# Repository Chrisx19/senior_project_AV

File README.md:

# CPP Senior Project

## December 2022 - May 2023
ROS Noetic control GPS autonomous vehicle using ATMega2560 and Jetson Nano. 

## Video Demo
**Autonomous Mode:**        https://youtu.be/Os8QsEWLSAU

**Controller Mode:**        https://youtu.be/IqCc2zWrYO0

**Test Controller Mode:**   https://youtu.be/60IaMCZQ1AA

### Mechanical 

### Electrical

**PCB Design**
  Reason initial design is included because of the mistakes my team learned while testing. Due to small traces with about 3 Amps going inside of our traces, it blew up and it came out of the PCB. Therefore, we learned from mistakes and calculated how much mil we need for our traces that can withstand about 4 Amps.
  
* **Initial Design: 30 mil traces**

* **Final Design: 150 mil traces**

### Software 
* **Communication:** 
  In order to have Jetson Nano and ATMega2560 talk to each other bi directionally, we used a customed UART protocol from ROS package called 'Rosserial.' Rosserial protocol was able to give us the ncecesity we need to transfer data from each other while autonomy. With rosserial, ATMega2560 became its own node and Jetson Nano has its main node and sub node. Nodes are basically scripts, which transfer myriad of data types from node to node.

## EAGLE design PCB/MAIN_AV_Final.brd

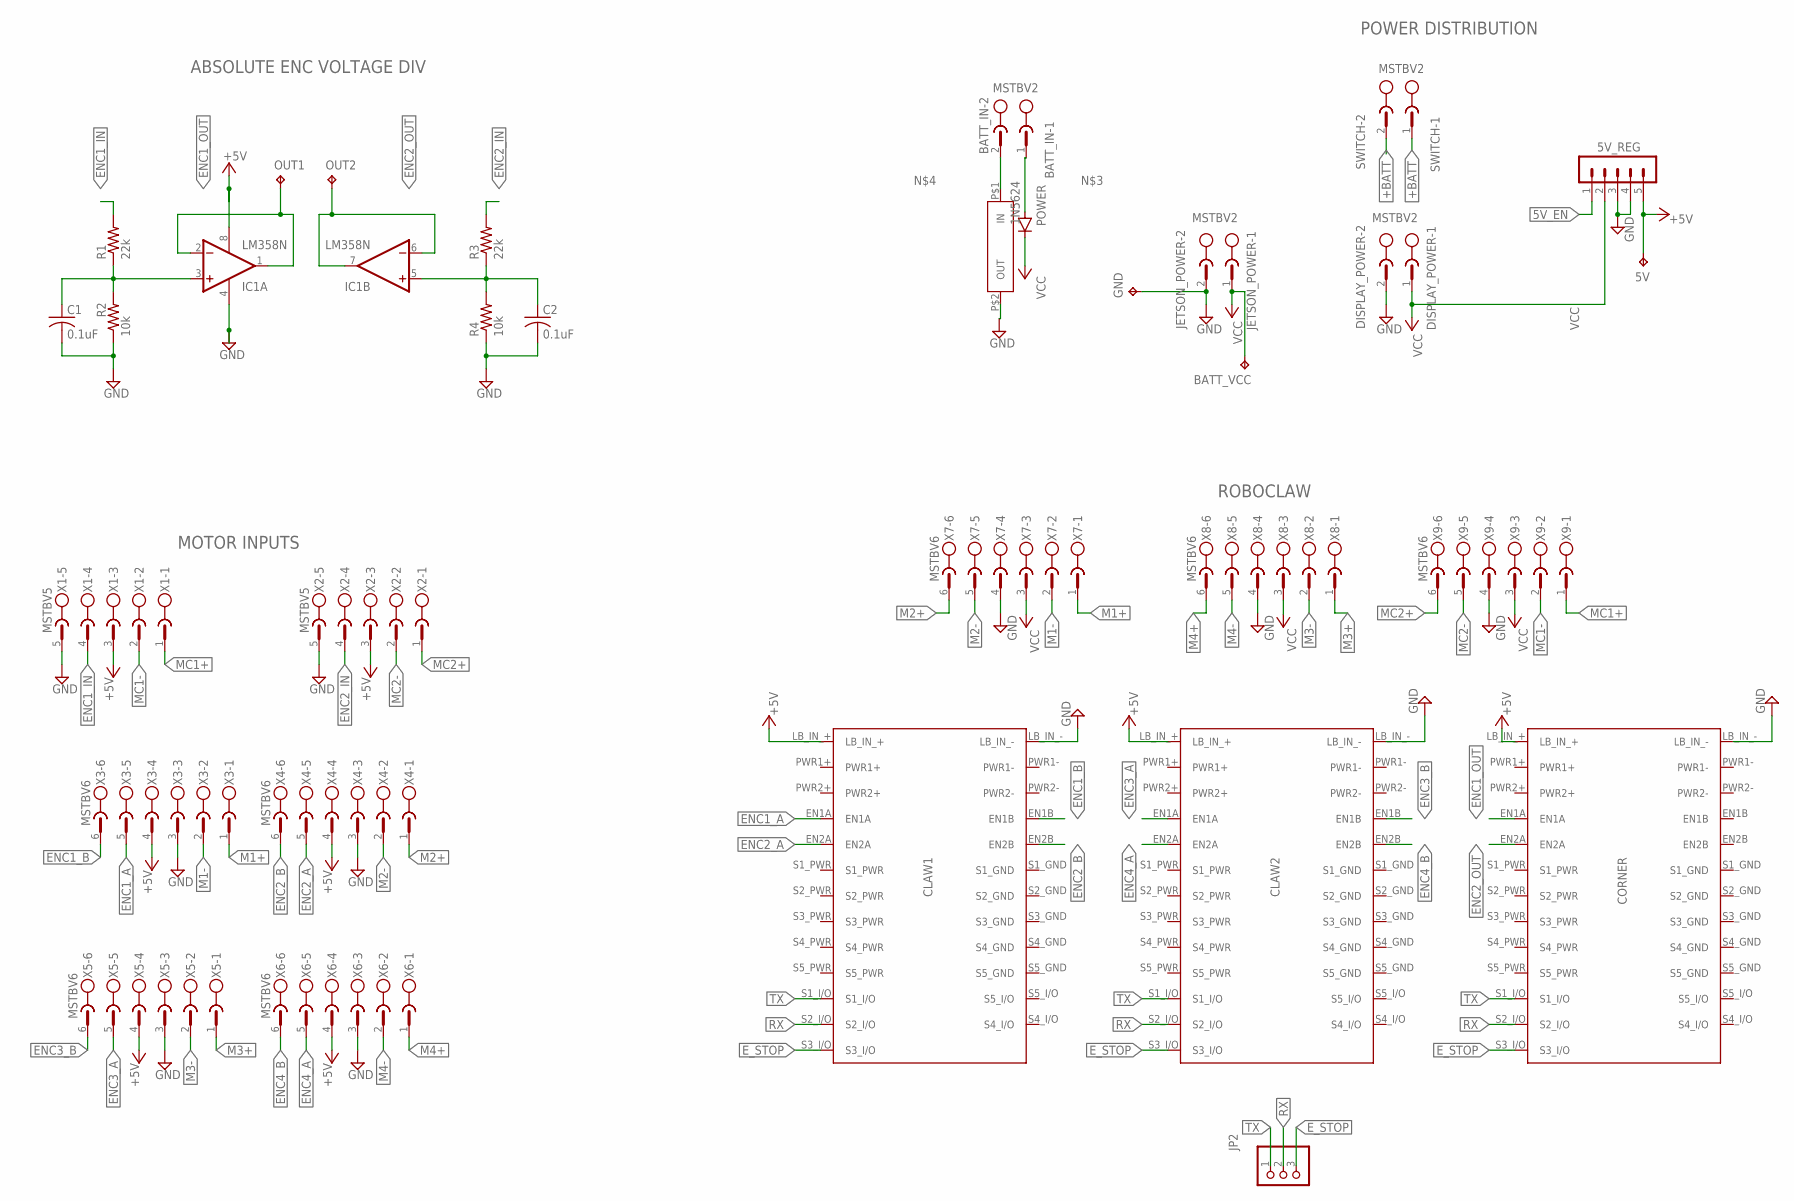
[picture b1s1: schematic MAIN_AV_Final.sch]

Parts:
5V: TPTP10SQ; TP10SQ
5V_REG: MA05-1
BATT_IN: MSTBV2
BATT_VCC: TPTP10SQ; TP10SQ
C1, C2: 0.1uF; C050-024X044
CLAW1, CLAW2: ROBOCLAW2X7A; ROBOCLAW
CORNER: ROBOCLAW2X7A; ROBOCLAW
DISPLAY_POWER: MSTBV2
GND: TPTP10SQ; TP10SQ
IC1: LM358N; DIL08
JETSON_POWER: MSTBV2
JP2: PINHD-1X3; 1X03
OUT1, OUT2: TPTP10SQ; TP10SQ
POWER: 1N5624; DO201-15
R1, R3: 22k; 0204/7
R2, R4: 10k; 0204/7
SWITCH: MSTBV2
U$1: FUSEHOLDER
X1, X2: MSTBV5
X3, X4, X5, X6, X7, X8, X9: MSTBV6

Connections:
5V_EN: 5V_REG.1
+5V: 5V.TP, 5V_REG.5, CLAW1.LB_IN_+, CLAW2.LB_IN_+, CORNER.LB_IN_+, IC1.8 (V+), X1.3, X2.3, X3.4, X4.4, X5.4, X6.4
+BATT: SWITCH.1, SWITCH.2
ENC1_A: CLAW1.EN1A, X3.5
ENC1_B: CLAW1.EN1B, X3.6
ENC1_IN: R1.2, X1.4
ENC1_OUT: CORNER.EN1A, IC1.1 (OUT), IC1.2 (-IN), OUT1.TP
ENC2_A: CLAW1.EN2A, X4.5
ENC2_B: CLAW1.EN2B, X4.6
ENC2_IN: R3.2, X2.4
ENC2_OUT: CORNER.EN2A, IC1.6 (-IN), IC1.7 (OUT), OUT2.TP
ENC3_A: CLAW2.EN1A, X5.5
ENC3_B: CLAW2.EN1B, X5.6
ENC4_A: CLAW2.EN2A, X6.5
ENC4_B: CLAW2.EN2B, X6.6
E_STOP: CLAW1.S3_I/O, CLAW2.S3_I/O, CORNER.S3_I/O, JP2.3
GND: 5V_REG.3, 5V_REG.4, C1.2, C2.2, CLAW1.LB_IN_-, CLAW2.LB_IN_-, CORNER.LB_IN_-, DISPLAY_POWER.2, GND.TP, IC1.4 (V-), JETSON_POWER.2, R2.1, R4.1, U$1.P$2 (OUT), X1.5, X2.5, X3.3, X4.3, X5.3, X6.3, X7.4, X8.4, X9.4
M1+: X3.1, X7.1
M1-: X3.2, X7.2
M2+: X4.1, X7.6
M2-: X4.2, X7.5
M3+: X5.1, X8.1
M3-: X5.2, X8.2
M4+: X6.1, X8.6
M4-: X6.2, X8.5
MC1+: X1.1, X9.1
MC1-: X1.2, X9.2
MC2+: X2.1, X9.6
MC2-: X2.2, X9.5
unnamed: C1.1, IC1.3 (+IN), R1.1, R2.2
unnamed: C2.1, IC1.5 (+IN), R3.1, R4.2
unnamed: BATT_IN.1, POWER.A
unnamed: BATT_IN.2, U$1.P$1 (IN)
RX: CLAW1.S2_I/O, CLAW2.S2_I/O, CORNER.S2_I/O, JP2.2
TX: CLAW1.S1_I/O, CLAW2.S1_I/O, CORNER.S1_I/O, JP2.1
VCC: 5V_REG.2, BATT_VCC.TP, DISPLAY_POWER.1, JETSON_POWER.1, POWER.C, X7.3, X8.3, X9.3

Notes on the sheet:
ABSOLUTE ENC VOLTAGE DIV
POWER DISTRIBUTION
MOTOR INPUTS
ROBOCLAW

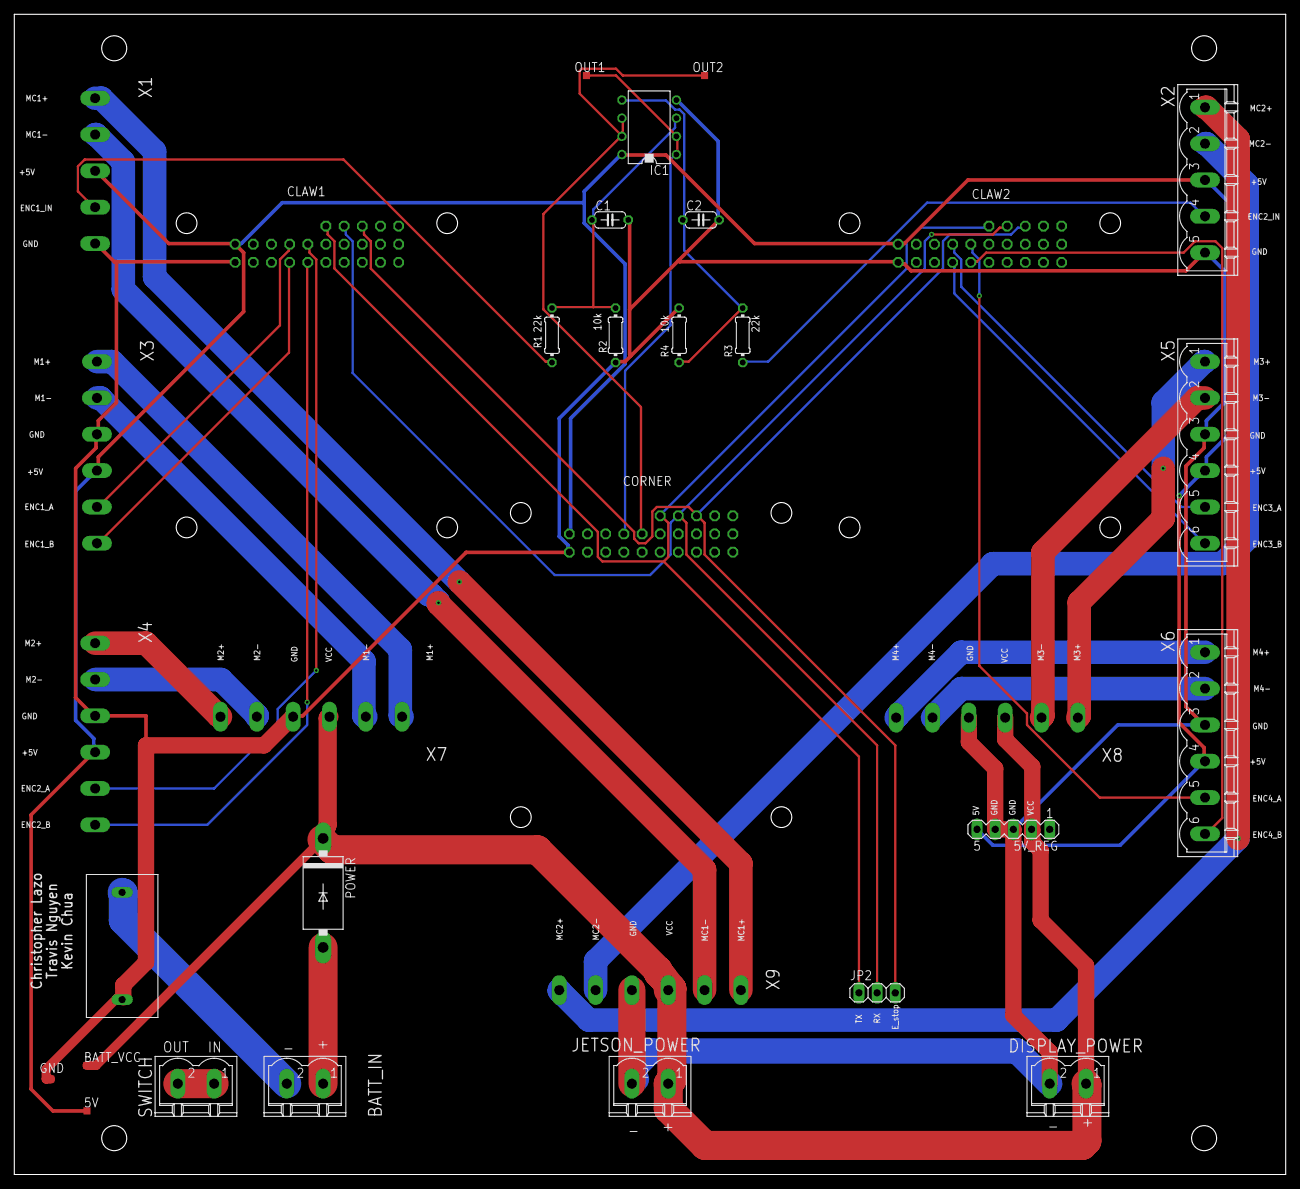
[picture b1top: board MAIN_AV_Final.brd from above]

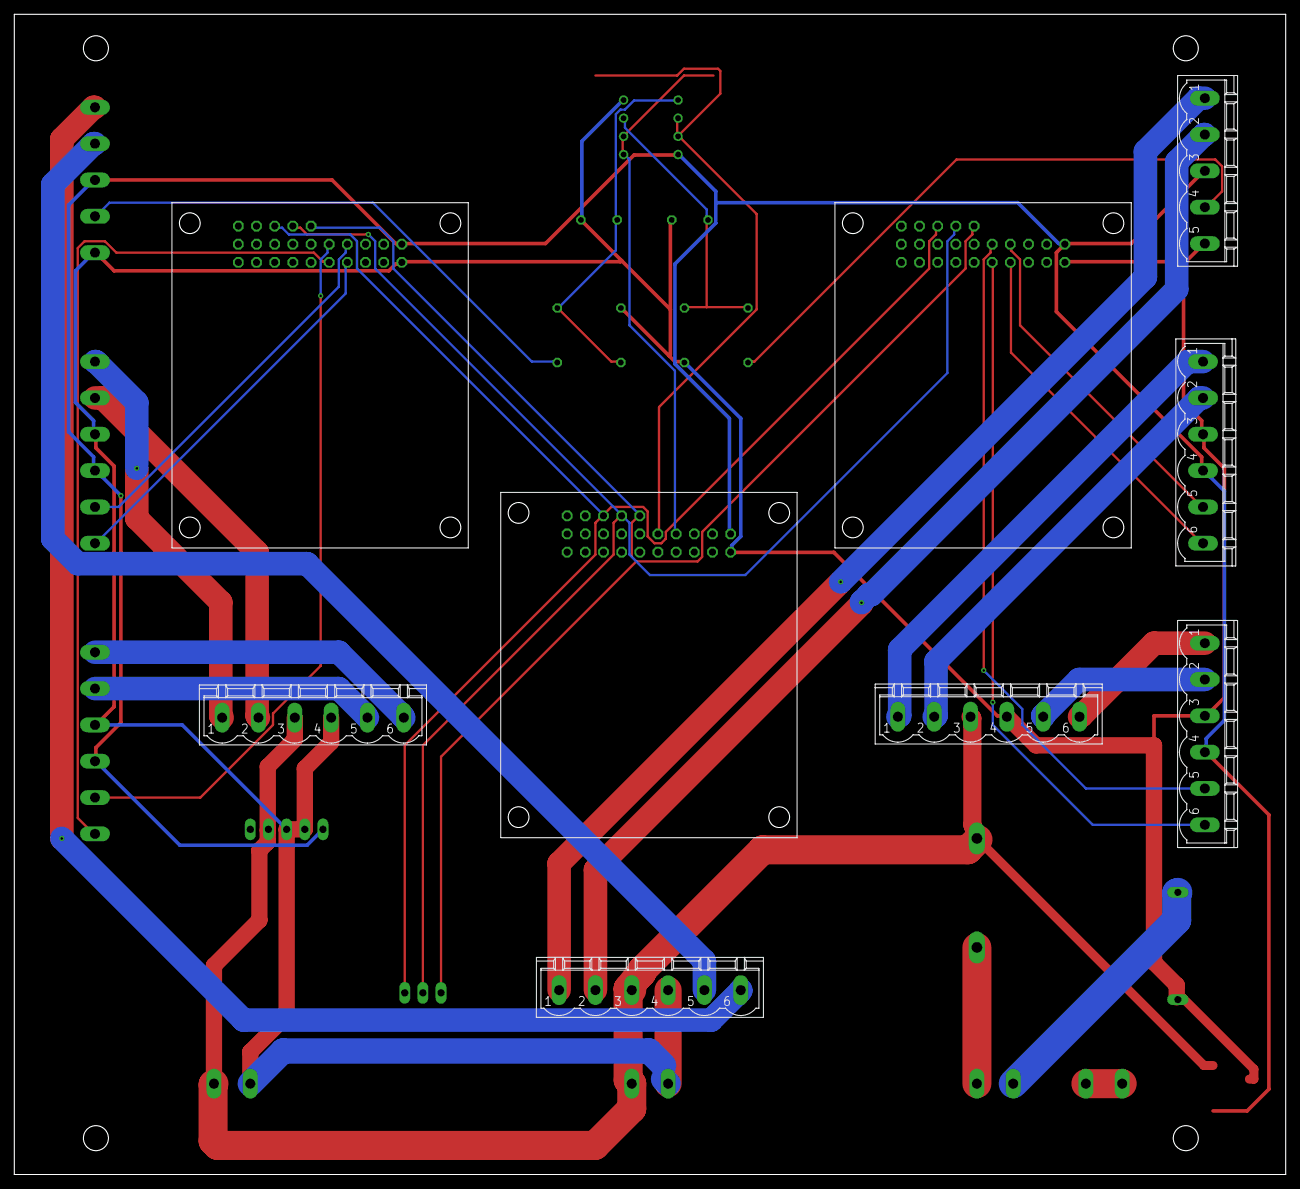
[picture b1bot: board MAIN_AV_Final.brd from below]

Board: 2 copper layers, 177.8 x 162.2 mm, 32 parts (9 on the bottom side), 35 nets.

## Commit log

2023-01-28 First
2023-04-05 Newest Update
2023-04-05 First Travis
2023-04-06 code_update
2023-04-06 test_encoder_val
2023-04-06 Encoder_add
2023-04-06 Added m/s conversion
2023-04-09 Convert QPPS -> m/s
2023-04-13 Trying to add pwm mode
2023-04-15 Sensor Update
2023-04-23 mechanical stuff
2023-04-23 Added Corner Assembly
2023-04-23 Added Wheel and rim
2023-04-25 Car_Kevin_Mod
2023-04-26 HL Software Update
2023-04-27 HL Script
2023-04-28 updat
2023-04-28 Added object detection and autonomus
2023-04-28 Final
2023-06-02 Create High level Software
2023-06-02 Create s
2023-06-02 LL_code
2023-10-14 Back_Up
2023-10-14 Fixed back Up
2023-10-23 Added Auto script run
2023-10-23 Fixed
2023-10-23 added arduino and jetson source codes for manual
2023-10-23 Format
2023-10-28 Added Shutdown using Controller
2023-10-28 Updated to manual
2023-10-28 Added Root
2023-10-28 Update joy_av.py for shutdown()
